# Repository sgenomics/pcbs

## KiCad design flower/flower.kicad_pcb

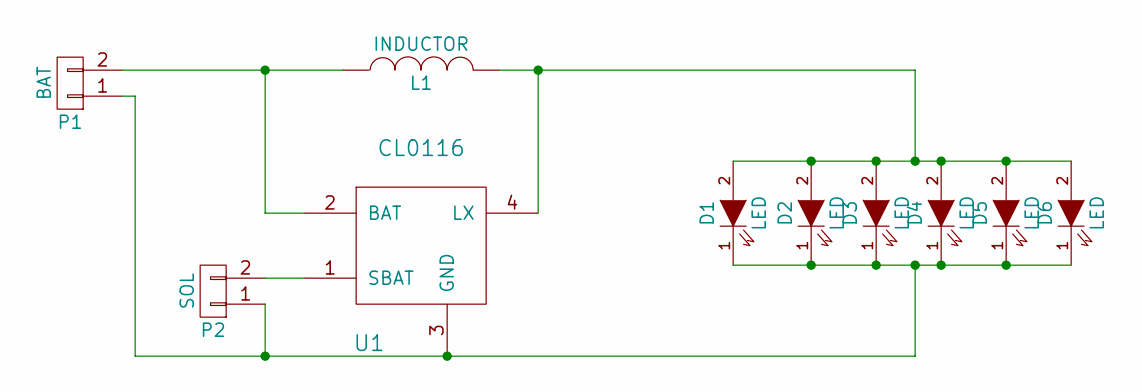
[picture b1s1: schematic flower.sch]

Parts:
D1, D2, D3, D4, D5, D6: LED; LED-3MM
L1: INDUCTOR; Resistor_Horizontal_RM10mm
P1: BAT; Socket_Strip_Straight_1x02
P2: SOL; Socket_Strip_Straight_1x02
U1: CL0116; TO94

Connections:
unnamed: D1.1 (K), D2.1 (K), D3.1 (K), D4.1 (K), D5.1 (K), D6.1 (K), P1.1, P2.1, U1.3 (GND)
unnamed: D1.2 (A), D2.2 (A), D3.2 (A), D4.2 (A), D5.2 (A), D6.2 (A), L1.2, U1.4 (LX)
unnamed: L1.1, P1.2, U1.2 (BAT)
unnamed: P2.2, U1.1 (SBAT)

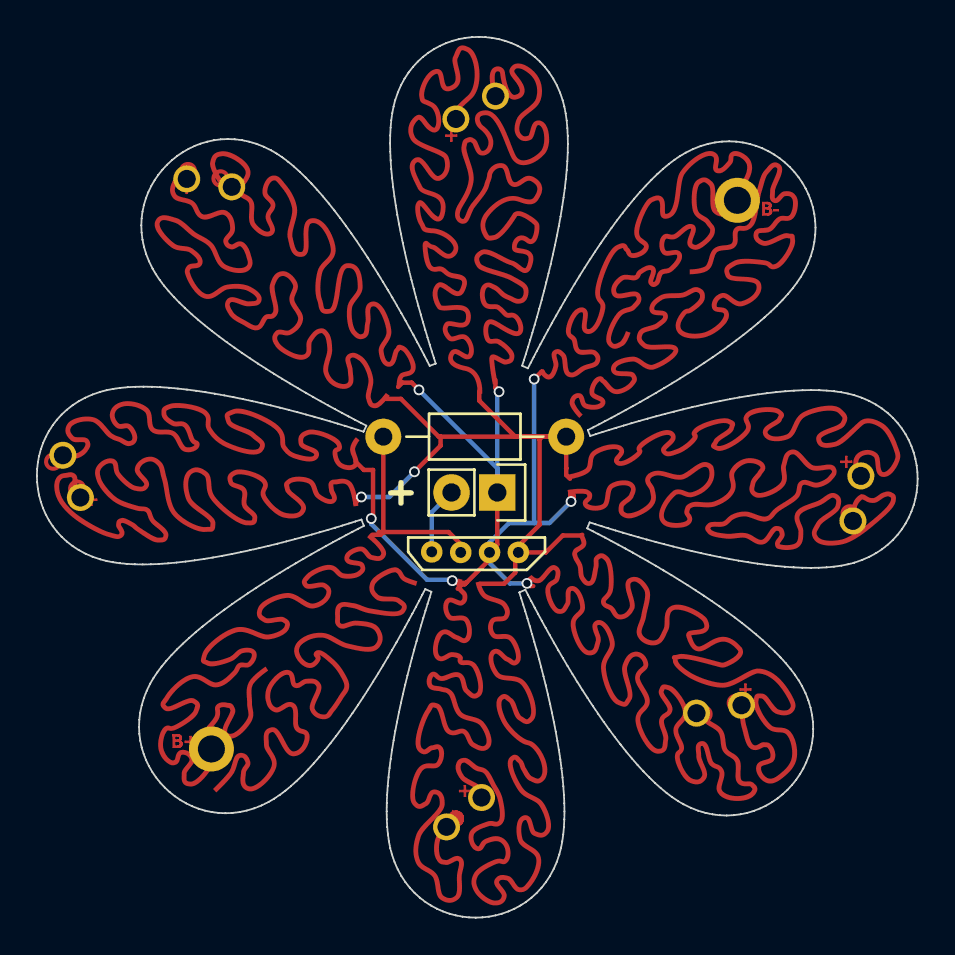
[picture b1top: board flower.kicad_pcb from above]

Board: 2 copper layers, 48.9 x 48.9 mm, 10 parts (0 on the bottom side), 4 nets.

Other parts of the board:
svg2mod: G***; svg2mod

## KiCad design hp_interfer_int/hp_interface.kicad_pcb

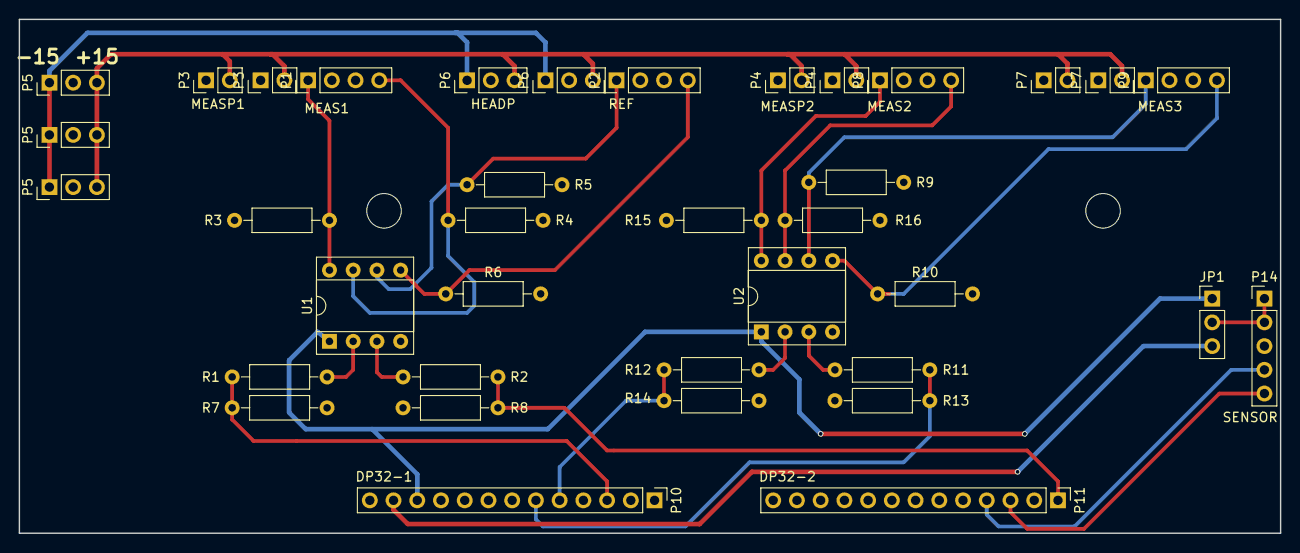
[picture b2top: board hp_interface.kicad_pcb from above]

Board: 2 copper layers, 135.0 x 55.0 mm, 37 parts (0 on the bottom side), 24 nets.

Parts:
JP1: JUMPER3; Socket_Strip_Straight_1x03_Pitch2.54mm
P1: MEAS1; Socket_Strip_Straight_1x04_Pitch2.54mm
P2: REF; Socket_Strip_Straight_1x04_Pitch2.54mm
P3, P3#2: MEASP1; Socket_Strip_Straight_1x02_Pitch2.54mm
P4, P4#2: MEASP2; Socket_Strip_Straight_1x02_Pitch2.54mm
P5, P5#2, P5#3: PWR; Socket_Strip_Straight_1x03_Pitch2.54mm
P6, P6#2: HEADP; Socket_Strip_Straight_1x03_Pitch2.54mm
P7, P7#2: MEASP3; Socket_Strip_Straight_1x02_Pitch2.54mm
P8: MEAS2; Socket_Strip_Straight_1x04_Pitch2.54mm
P9: MEAS3; Socket_Strip_Straight_1x04_Pitch2.54mm
P10: DP32-1; Socket_Strip_Straight_1x13_Pitch2.54mm
P11: DP32-2; Socket_Strip_Straight_1x13_Pitch2.54mm
P14: SENSOR; Socket_Strip_Straight_1x05_Pitch2.54mm
R1, R2, R3, R4, R5, R6, R9, R10, R11, R12, R15, R16: 150; R_Axial_DIN0207_L6.3mm_D2.5mm_P10.16mm_Horizontal
R7, R8, R13, R14: 330; R_Axial_DIN0207_L6.3mm_D2.5mm_P10.16mm_Horizontal
U1, U2: UA9637; DIP-8_W7.62mm_Socket

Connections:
+3V3: JP1.3, P10.12
+5V: JP1.1, P10.11, U1.1, U2.1
+15V: P3.2, P3#2.2, P4.2, P4#2.2, P5.3, P5#2.3, P5#3.3, P6.3, P6#2.3, P7.2, P7#2.2
-15V: P5.1, P5#2.1, P5#3.1, P6.1, P6#2.1
GND: P1.2, P1.3, P2.2, P2.3, P3.1, P3#2.1, P4.1, P4#2.1, P5.2, P5#2.2, P5#3.2, P6.2, P6#2.2, P7.1, P7#2.1, P8.2, P8.3, P9.2, P9.3, P10.13, P14.3, R3.1, R4.2, R5.1, R6.2, R7.1, R8.1, R9.1, R10.2, R13.1, R14.1, R15.1, R16.2, U1.4, U2.4
unnamed: JP1.2, P14.1, P14.2
unnamed: P1.1, R3.2, U1.8
unnamed: P1.4, R4.1, U1.7
unnamed: P2.1, R5.2, U1.6
unnamed: P2.4, R6.1, U1.5
unnamed: P8.1, R15.2, U2.8
unnamed: P8.4, R16.1, U2.7
unnamed: P9.1, R9.2, U2.6
unnamed: P9.4, R10.1, U2.5
unnamed: R1.1, U1.2
unnamed: R2.1, U1.3
unnamed: R11.1, U2.3
unnamed: R12.1, U2.2
RB0: P10.3, R1.2, R7.2
RB2: P10.5, R12.2, R14.2
RB3: P10.6, R11.2, R13.2
RB5: P11.1, R2.2, R8.2
RB8: P11.3, P14.5
RB9: P11.4, P14.4

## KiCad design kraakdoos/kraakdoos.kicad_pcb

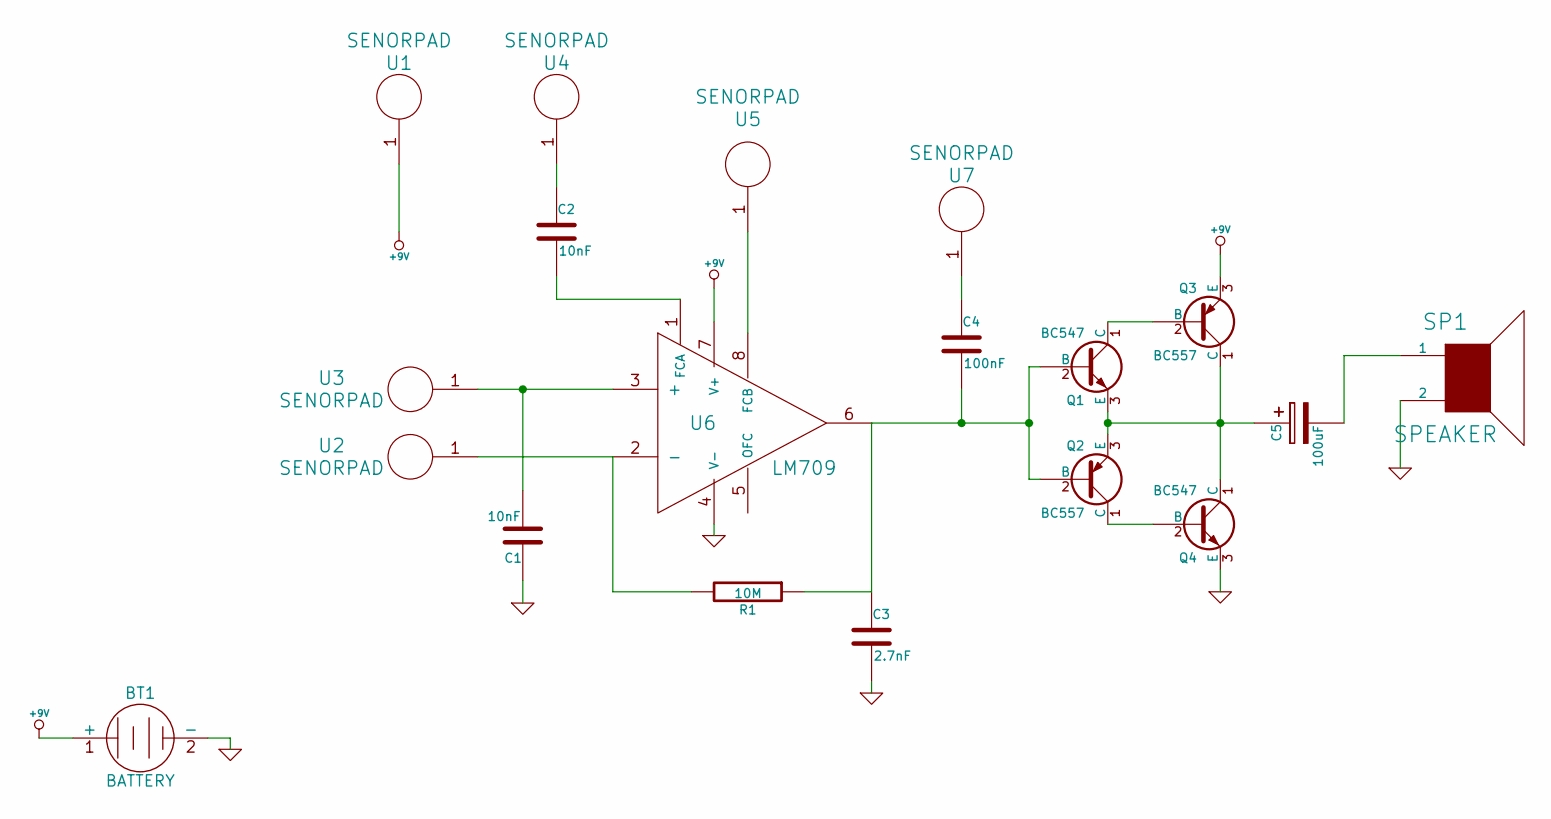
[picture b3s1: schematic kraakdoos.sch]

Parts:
BT1: BATTERY
C1, C2: 10nF; C_Disc_D6_P5
C3: 2.7nF; C_Disc_D6_P5
C4: 100nF; C_Disc_D6_P5
C5: 100uF; C_Radial_D5_L11_P2.5
Q1, Q4: BC547; TO-92_Molded_Wide
Q2, Q3: BC557; TO-92_Molded_Wide
R1: 10M; Resistor_Horizontal_RM10mm
SP1: SPEAKER; Socket_Strip_Straight_1x02
U1, U2, U3, U4, U5, U7: SENORPAD; SENSORPAD
U6: LM709; H08

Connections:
+9V: BT1.1 (+), Q3.3 (E), U1.1, U6.7 (V+)
GND: BT1.2 (-), C1.1, C3.2, Q4.3 (E), SP1.2, U6.4 (V-); also elsewhere on the board
unnamed: C1.2, U3.1, U6.3 (+)
unnamed: C2.1, U4.1
unnamed: C2.2, U6.1 (FCA)
unnamed: C3.1, C4.2, Q1.2 (B), Q2.2 (B), R1.1, U6.6
unnamed: C4.1, U7.1
unnamed: C5.1, Q1.3 (E), Q2.3 (E), Q3.1 (C), Q4.1 (C)
unnamed 8: C5.2, SP1.1; also elsewhere on the board
unnamed: Q1.1 (C), Q3.2 (B)
unnamed: Q2.1 (C), Q4.2 (B)
unnamed: R1.2, U2.1, U6.2 (-)
unnamed: U5.1, U6.8 (FCB)

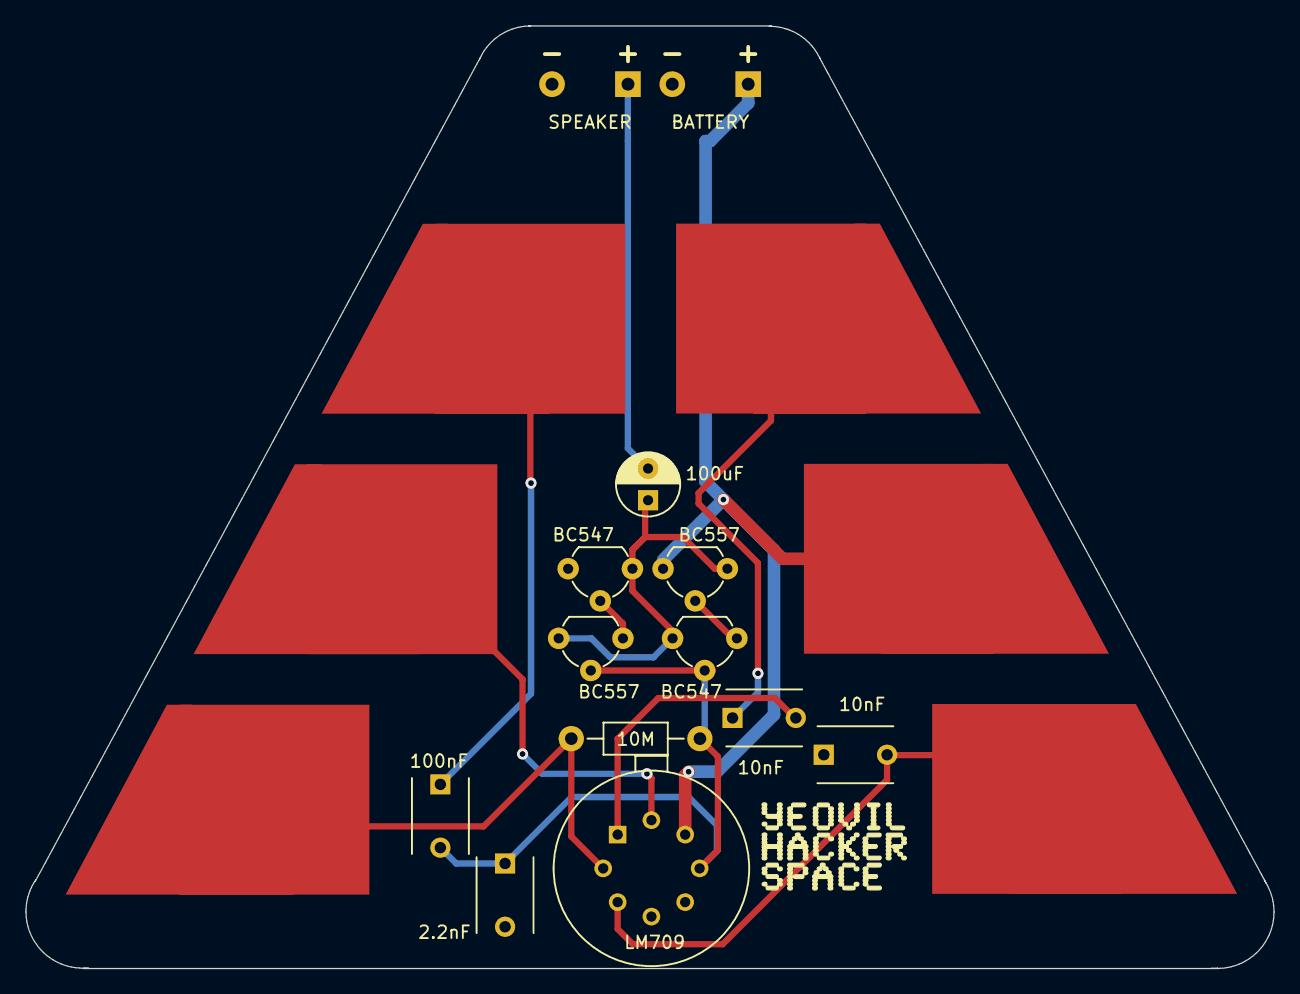
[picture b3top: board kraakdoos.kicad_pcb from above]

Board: 2 copper layers, 98.6 x 74.5 mm, 19 parts (0 on the bottom side), 13 nets.

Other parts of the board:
SPEAKER: SPEAKER; Socket_Strip_Straight_1x02

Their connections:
GND: SPEAKER.2; also elsewhere on the board
unnamed 8: SPEAKER.1; also elsewhere on the board

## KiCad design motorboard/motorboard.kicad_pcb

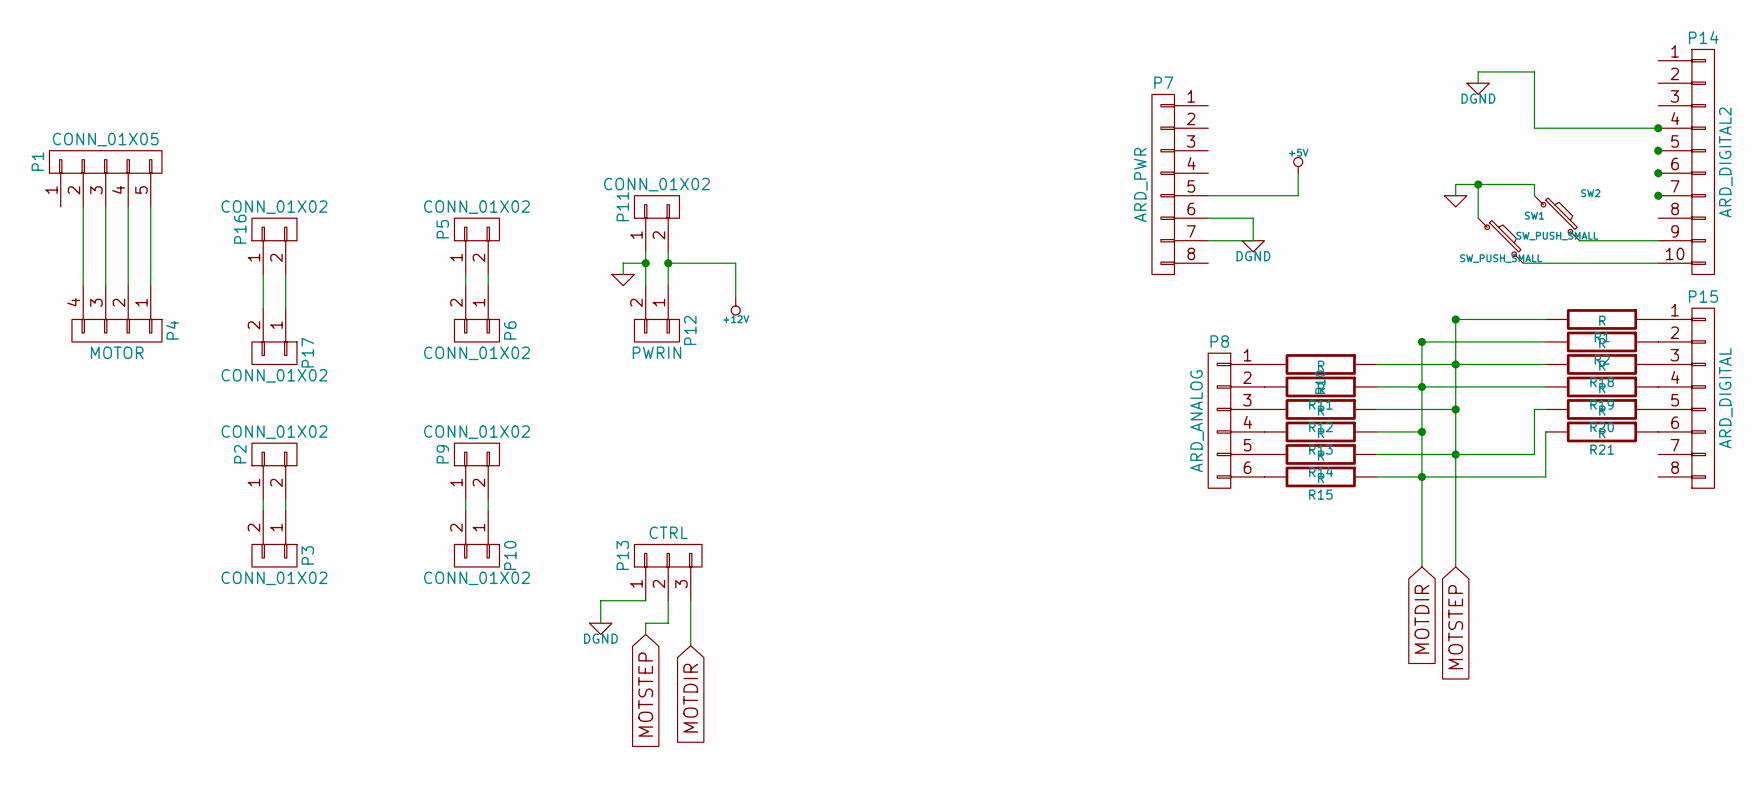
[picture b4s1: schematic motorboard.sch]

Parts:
P1: CONN_01X05; molex1445055
P2, P3, P5, P6, P9, P10, P16, P17: CONN_01X02; Pin_Header_Straight_1x02
P4: MOTOR; Pin_Header_Straight_1x04
P7: ARD_PWR; Pin_Header_Straight_1x08
P8: ARD_ANALOG; Pin_Header_Straight_1x06
P11: CONN_01X02; PWR
P12: PWRIN; Pin_Header_Straight_1x02
P13: CTRL; Pin_Header_Straight_1x03
P14: ARD_DIGITAL2; Pin_Header_Straight_1x10
P15: ARD_DIGITAL; Pin_Header_Straight_1x08
R1, R2, R10, R11, R12, R13, R14, R15, R18, R19, R20, R21: R; R_0805_HandSoldering
SW1, SW2: SW_PUSH_SMALL; SW

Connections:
+12V: P11.2, P12.1; also elsewhere on the board
DGND: P7.6, P7.7, P13.1, P14.4
GND: P11.1, P12.2, SW1.1, SW2.1; also elsewhere on the board
MOTDIR: P13.3, R2.2, R11.1, R13.1, R15.1, R19.2, R21.2
MOTSTEP: P13.2, R1.2, R10.1, R12.1, R14.1, R18.2, R20.2
unnamed: P1.2, P4.4
unnamed: P1.3, P4.3
unnamed: P1.4, P4.2
unnamed: P1.5, P4.1
unnamed: P2.1, P3.2
unnamed: P2.2, P3.1
unnamed: P5.1, P6.2
unnamed: P5.2, P6.1
unnamed: P8.1, R10.2
unnamed: P8.2, R11.2
unnamed: P8.3, R12.2
unnamed: P8.4, R13.2
unnamed: P8.5, R14.2
unnamed: P8.6, R15.2
unnamed: P9.2, P10.1
unnamed: P9.1, P10.2
unnamed: P14.9, SW2.2
unnamed: P14.10, SW1.2
unnamed: P15.1, R1.1
unnamed: P15.2, R2.1
unnamed: P15.3, R18.1
unnamed: P15.4, R19.1
unnamed: P15.5, R20.1
unnamed: P15.6, R21.1
unnamed: P16.1, P17.2
unnamed: P16.2, P17.1

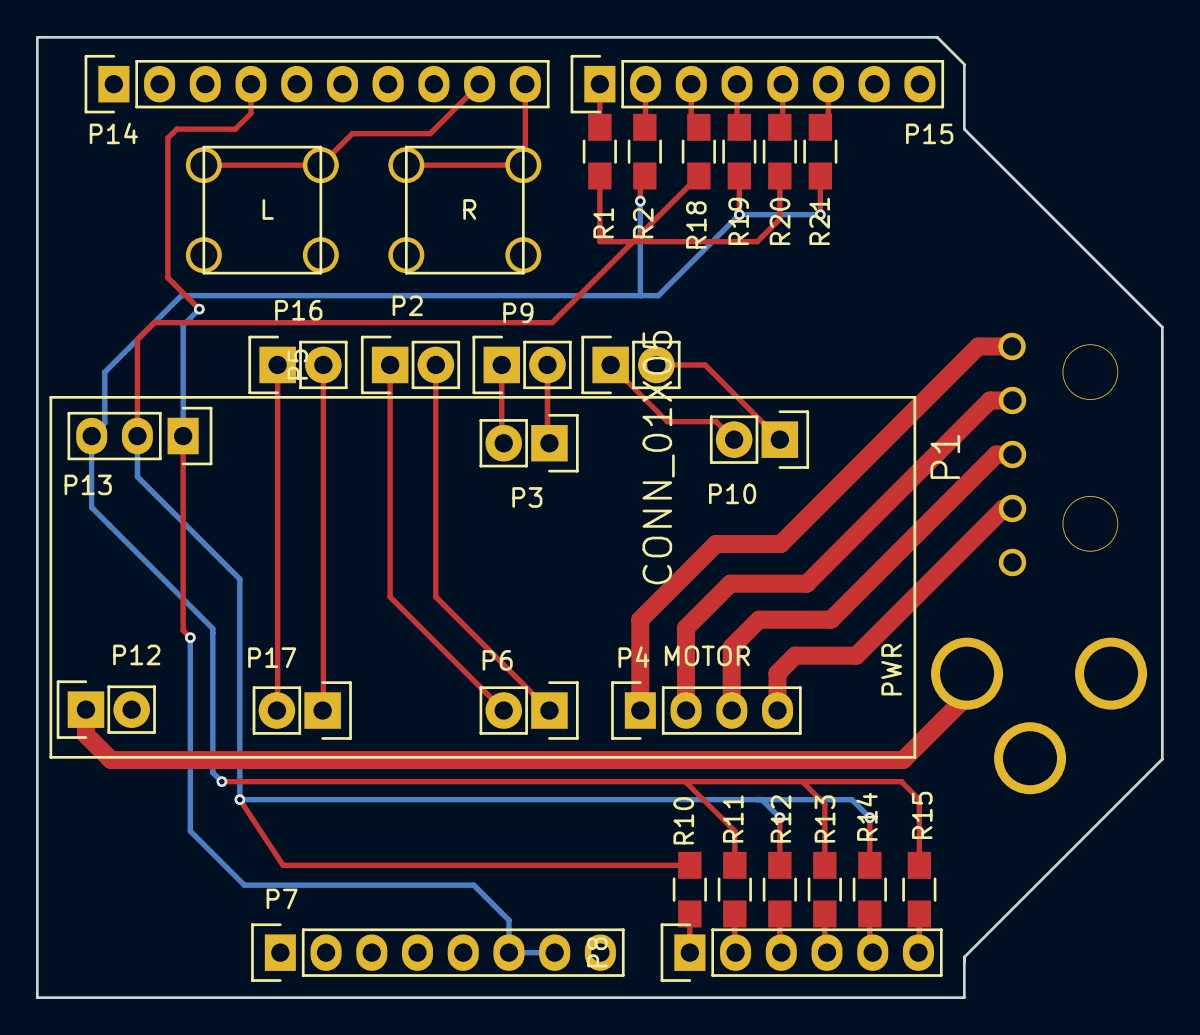
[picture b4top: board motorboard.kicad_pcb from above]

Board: 2 copper layers, 62.5 x 53.3 mm, 31 parts (0 on the bottom side), 31 nets.

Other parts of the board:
PWR: CONN_01X02; PWR

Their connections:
+12V: PWR.2; also elsewhere on the board
GND: PWR.1; also elsewhere on the board

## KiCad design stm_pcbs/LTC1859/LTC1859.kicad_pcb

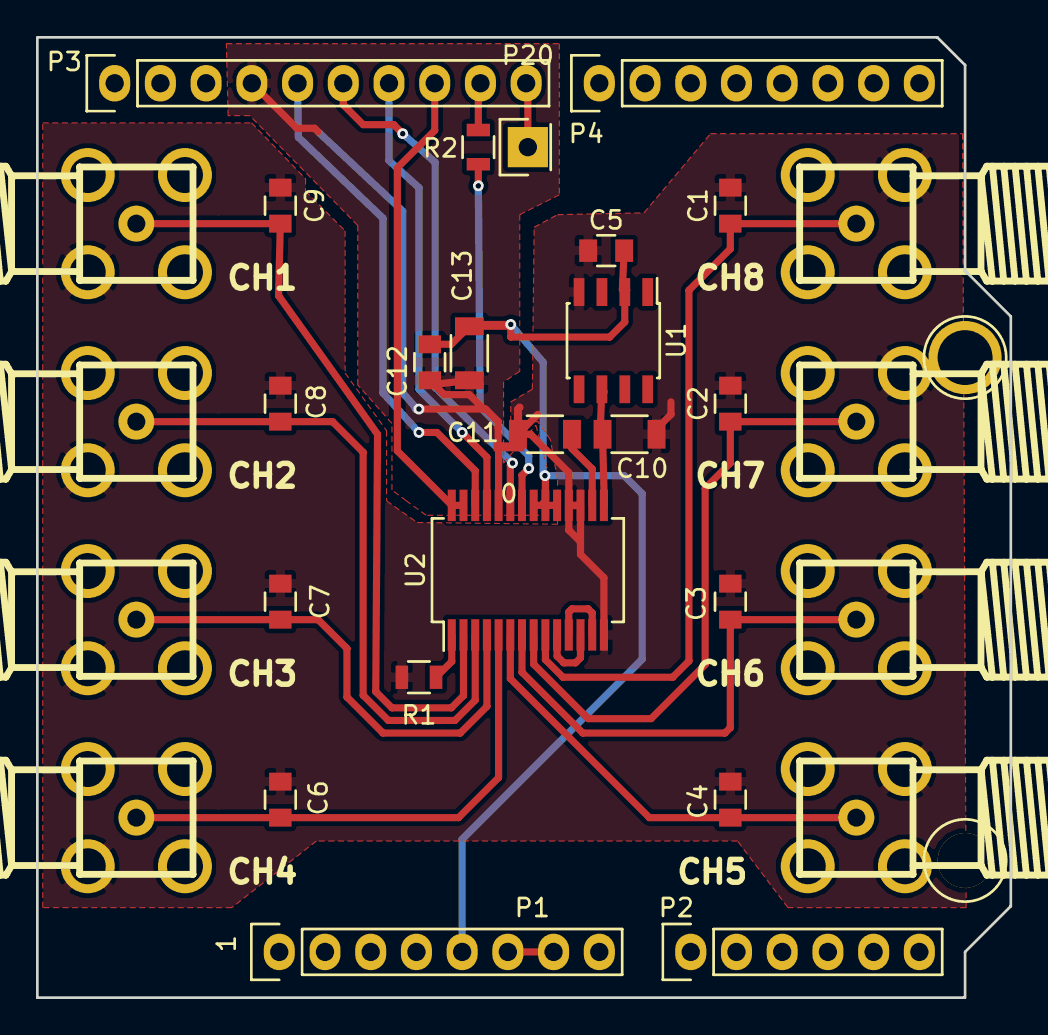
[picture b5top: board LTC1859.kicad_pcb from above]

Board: 2 copper layers, 54.1 x 53.3 mm, 33 parts (0 on the bottom side), 23 nets.

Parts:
C1, C2, C3, C4, C6, C7, C8, C9: 1000pF; C_0805
C5, C12: 0.1uF; C_0805
C10: 4.7uF; C_1206
C11, C13: 10uF; C_1206
CH1, CH2, CH3, CH4, CH5, CH6, CH7, CH8: BNC; SMA
P1: Power; Socket_Strip_Arduino_1x08
P2: Analog; Socket_Strip_Arduino_1x06
P3: Digital; Socket_Strip_Arduino_1x10
P4: Digital; Socket_Strip_Arduino_1x08
P6, P8: CONN_1; Arduino_1pin
P20: CONN_01X01; Socket_Strip_Straight_1x01
R1, R2: 0; R_0805
R3: 0; 0Ohm
U1: LT1019ACS8; SOIC-8-1EP_3.9x4.9mm_Pitch1.27mm
U2: LTC1859; SSOP-28_5.3x10.2mm_Pitch0.65mm

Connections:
+5V: C5.1, C12.1, C13.1, P1.5, U1.2, U2.19, U2.20, U2.21
AGND: C1.2, C2.2, C3.2, C4.2, C5.2, C6.2, C7.2, C8.2, C9.2, C10.2, C11.2, CH1.2, CH2.2, CH3.2, CH4.2, CH5.2, CH6.2, CH7.2, CH8.2, R1.2, R3.2, U1.4, U2.14, U2.17, U2.18
DGND: C12.2, C13.2, P1.6, P1.7, P3.4, R3.1, U2.24
unnamed: C1.1, CH8.1, U2.9
unnamed: C2.1, CH7.1, U2.8
unnamed: C3.1, CH6.1, U2.7
unnamed: C4.1, CH5.1, U2.6
unnamed: C6.1, CH4.1, U2.5
unnamed: C7.1, CH3.1, U2.4
unnamed: C8.1, CH2.1, U2.3
unnamed: C9.1, CH1.1, U2.2
unnamed: C10.1, U1.6, U2.15
unnamed: C11.1, U2.16
unnamed: P3.5, U2.26
unnamed: P3.6, U2.23
unnamed: P3.7, U2.25
unnamed: P3.8, U2.27
unnamed: P3.9, R2.1
unnamed: P3.10, P20.1
unnamed: R1.1, U2.1
unnamed: R2.2, U2.22
unnamed: U2.10, U2.12
unnamed: U2.11, U2.13

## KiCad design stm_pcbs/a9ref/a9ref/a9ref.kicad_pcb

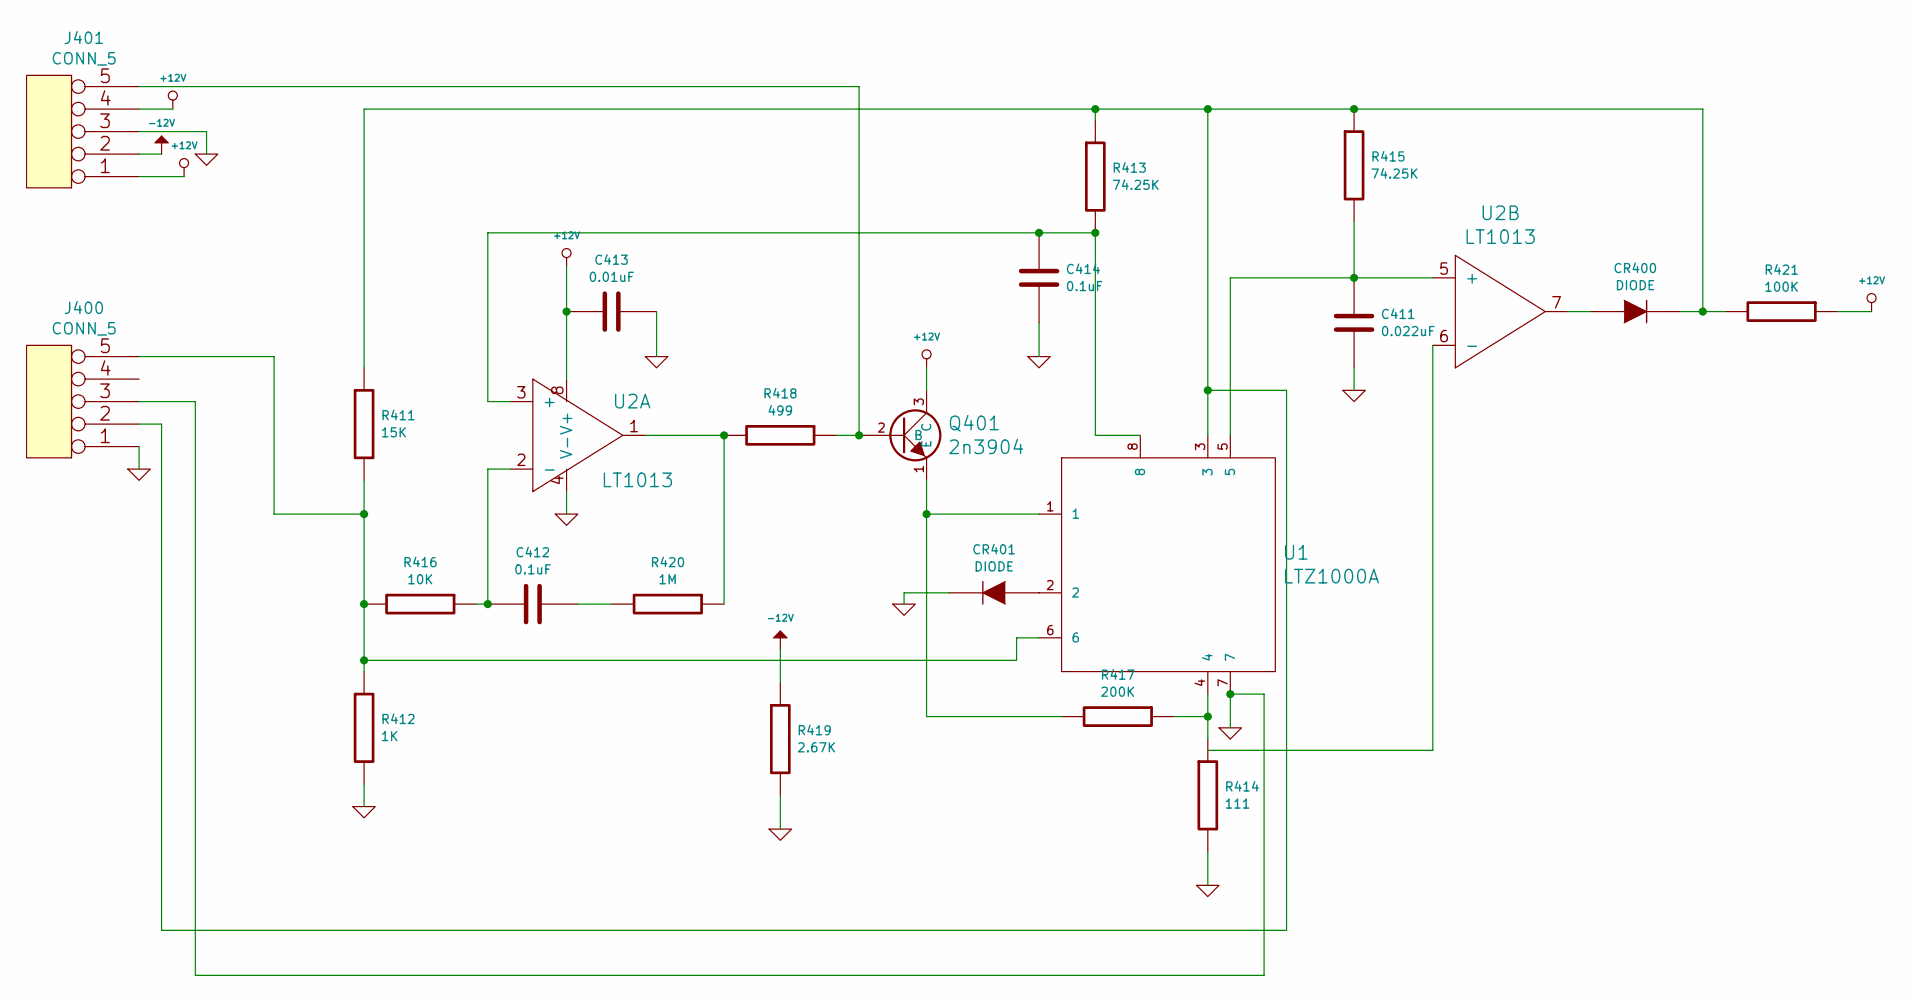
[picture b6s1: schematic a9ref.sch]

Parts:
C411: 0.022uF; 0.5inch_resistor
C412, C414: 0.1uF; 0.5inch_resistor
C413: 0.01uF; 0.5inch_resistor
CR400, CR401: DIODE; D_DO-35_SOD27_P10.16mm_Horizontal
J400, J401: CONN_5; CONN5R
Q401: 2n3904; TO-92_Inline_Wide
R411: 15K; R_Box_L8.4mm_W2.5mm_P5.08mm
R412: 1K; R_Box_L8.4mm_W2.5mm_P5.08mm
R413, R415: 74.25K; 0.5inch_resistor
R414: 111; R_Box_L8.4mm_W2.5mm_P5.08mm
R416: 10K; 0.5inch_resistor
R417: 200K; 0.5inch_resistor
R418: 499; 0.5inch_resistor
R419: 2.67K; 0.5inch_resistor
R420: 1M; 0.5inch_resistor
R421: 100K; 0.5inch_resistor
U1: LTZ1000A; TO-5-8
U2: LT1013; DIP-8_W7.62mm

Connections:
+12V: C413.2, J401.1, J401.4, Q401.3 (C), R421.1, U2.8 (V+)
-12V: J401.2, R419.1
GND: C411.2, C413.1, C414.2, CR401.2 (K), J400.1, J400.3, J401.3, R412.2, R414.2, R419.2, U1.7, U2.4 (V-)
unnamed: C411.1, R415.2, U1.5, U2.5 (+)
unnamed: C412.1, R420.2
unnamed: C412.2, R416.1, U2.2 (-)
unnamed: C414.1, R413.2, U1.8, U2.3 (+)
unnamed: CR400.1 (A), U2.7
unnamed: CR400.2 (K), J400.2, R411.1, R413.1, R415.1, R421.2, U1.3
unnamed: CR401.1 (A), U1.2
unnamed: J400.5, R411.2, R412.1, R416.2, U1.6
unnamed: J401.5, Q401.2 (B), R418.1
unnamed: Q401.1 (E), R417.2, U1.1
unnamed: R414.1, R417.1, U1.4
unnamed: R418.2, R420.1, U2.1

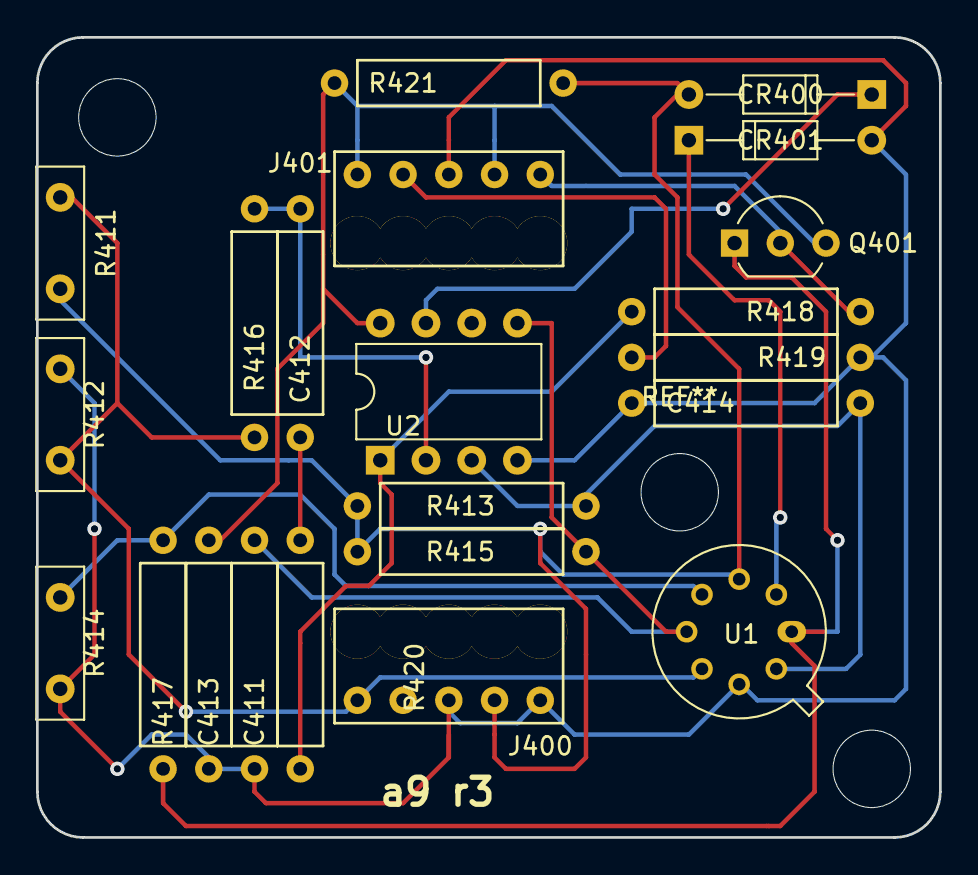
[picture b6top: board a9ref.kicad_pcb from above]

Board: 2 copper layers, 50.2 x 44.5 mm, 22 parts (0 on the bottom side), 15 nets.

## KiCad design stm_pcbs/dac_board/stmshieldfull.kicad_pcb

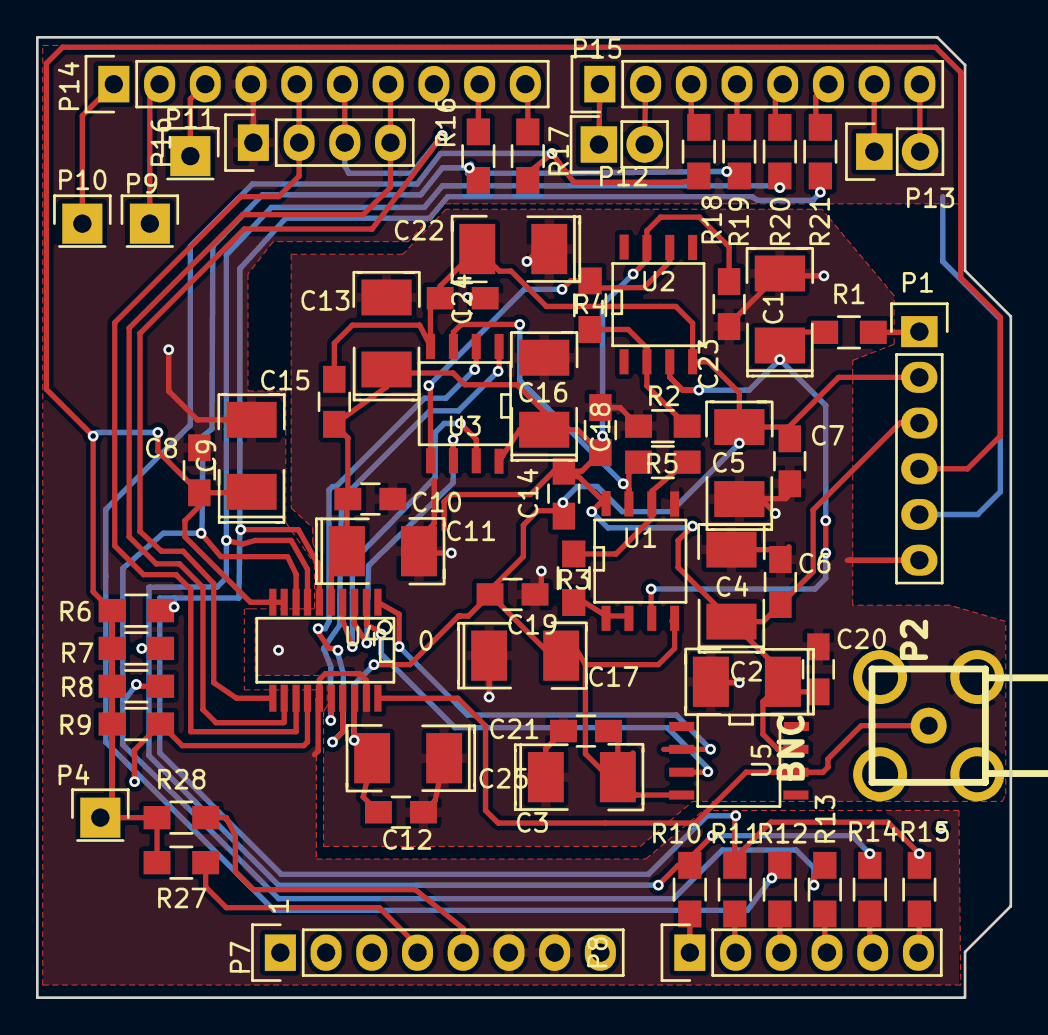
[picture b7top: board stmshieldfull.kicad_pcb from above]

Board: 2 copper layers, 54.1 x 53.3 mm, 67 parts (0 on the bottom side), 47 nets.

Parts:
C1, C2, C3, C4, C5, C9, C11, C13, C16, C17, C22, C25: 10uF; SMD-1210_Pol
C6, C7, C8, C10, C12, C14, C15, C18, C19, C20, C21, C23, C24: 0.1uF; C_0805_HandSoldering
P1: REFVHEAD; Pin_Header_Straight_1x06
P2: BNC; SMA
P4, P9, P10, P11: CONN_01X01; Pin_Header_Straight_1x01
P7: ARD_PWR; Pin_Header_Straight_1x08
P8: ARD_ANALOG; Pin_Header_Straight_1x06
P12, P13: CONN_01X02; Pin_Header_Straight_1x02
P14: ARD_DIGITAL2; Pin_Header_Straight_1x10
P15: ARD_DIGITAL; Pin_Header_Straight_1x08
P16: CONN_01X04; Pin_Header_Straight_1x04
R1: 1.5k; R_0805_HandSoldering
R2, R3, R4: 1K; R_0805_HandSoldering
R5: 2K; R_0805_HandSoldering
R6, R7, R8, R9: 10K; R_0805_HandSoldering
R10, R11, R12, R13, R14, R15, R16, R17, R18, R19, R20, R21: R; R_0805_HandSoldering
R22: 0; 0Ohm
R27, R28: 0; R_0805_HandSoldering
U1, U3: AD8676; SOIC-8
U2, U5: AD8675; SOIC-8
U4: AD5791; SSOP-20

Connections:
3.3V: C8.2, C9.1, P1.4, P4.1, R6.1, R7.1, R8.1, R9.1, R27.1, R28.1, U4.9, U4.10
5VREF: P1.1, R1.2
+10VREF: R4.1, U2.6, U3.5
+14V: C2.1, C4.1, C6.1, C10.2, C11.1, C13.1, C14.1, C15.1, C16.1, C18.1, C20.1, C23.1, P1.3, U1.8, U2.7, U3.8, U4.5, U5.7
-10VREF: R5.1, U1.7, U3.3
-14V: C3.2, C5.2, C7.1, C12.2, C14.2, C15.2, C17.2, C19.1, C21.1, C22.2, C24.1, C25.2, P1.2, U1.4, U2.4, U3.4, U4.18, U5.4
AGND: C1.2, C2.2, C3.1, C4.2, C5.1, C6.2, C7.2, C10.1, C11.2, C12.1, C13.2, C16.2, C17.1, C18.2, C19.2, C20.2, C21.2, C22.1, C23.2, C24.2, C25.1, P1.6, P2.2, R2.2, R22.2, U1.5, U4.19
CLR: R7.2, R10.1, R14.1, R20.2, U4.7
DGND: C8.1, C9.2, P1.5, P7.6, P7.7, P14.4, P16.1, R22.1, U4.15
LDAC: R8.2, R13.1, R16.2, R19.2, U4.8
unnamed: C1.1, R1.1, U1.3, U2.3
unnamed: P2.1, U4.20, U5.6
unnamed: U4.2, U5.3
unnamed: P7.4, R27.2
unnamed: P7.5, R28.2
unnamed: P8.1, R10.2
unnamed: P8.2, R11.2
unnamed: P8.3, R12.2
unnamed: P8.4, R13.2
unnamed: P8.5, R14.2
unnamed: P8.6, R15.2
unnamed: P10.1, P14.1
unnamed: P11.1, P14.3
unnamed: P12.1, P15.1
unnamed: P12.2, P15.2
unnamed: P13.1, P15.7
unnamed: P13.2, P15.8
unnamed: P9.1, P14.2
unnamed: P14.9, R16.1
unnamed: P14.10, R17.1
unnamed: P15.3, R18.1
unnamed: P15.4, R19.1
unnamed: P15.5, R20.1
unnamed: P15.6, R21.1
unnamed: R2.1, R4.2, U2.2
unnamed: R3.1, R5.2, U1.6
unnamed: R3.2, U1.1, U1.2
unnamed: U3.1, U4.16
unnamed: U3.2, U4.17
unnamed: U3.6, U4.3
unnamed: U3.7, U4.4
unnamed: U4.1, U5.2
RESET: R6.2, R11.1, R15.1, R21.2, U4.6
SCLK: P14.5, P16.2, U4.13
SDIN: P14.7, P16.4, U4.12
SDO: P14.6, P16.3, U4.11
SYNC: R9.2, R12.1, R17.2, R18.2, U4.14

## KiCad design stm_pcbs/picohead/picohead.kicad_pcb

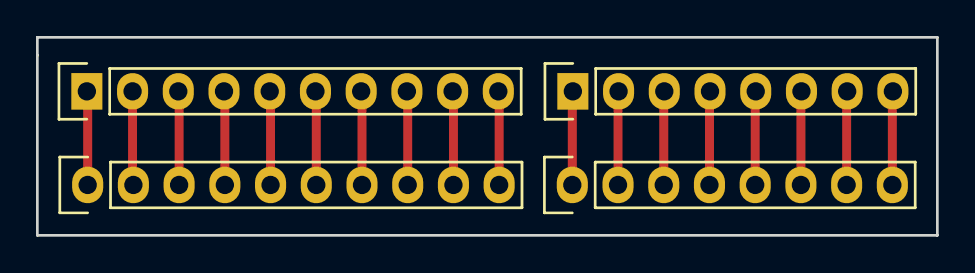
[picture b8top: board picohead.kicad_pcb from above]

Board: 2 copper layers, 50.0 x 11.0 mm, 4 parts (0 on the bottom side), 18 nets.

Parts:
P1: CONN_01X10; Socket_Strip_Straight_1x10
P2: CONN_01X08; Socket_Strip_Straight_1x08
P3: Digital; Socket_Strip_Arduino_1x10
P4: Digital; Socket_Strip_Arduino_1x08

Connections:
/0(Rx): P2.8, P4.8
/1(Tx): P2.7, P4.7
/2: P2.6, P4.6
/3(**): P2.5, P4.5
/4: P2.4, P4.4
/5(**): P2.3, P4.3
/6(**): P2.2, P4.2
/7: P2.1, P4.1
/8: P1.10, P3.10
/9(**): P1.9, P3.9
/10(**/SS): P1.8, P3.8
/11(**/MOSI): P1.7, P3.7
/12(MISO): P1.6, P3.6
/13(SCK): P1.5, P3.5
/A4(SDA): P1.2, P3.2
/A5(SCL): P1.1, P3.1
/AREF: P1.3, P3.3
GND: P1.4, P3.4
